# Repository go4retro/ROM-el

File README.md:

# ROM Eliminator (ROM-el)

FLASH ROM replacement devices for various ROM and EPROM familes.

## 2364 ROM-el

## 23128 ROM-el

## 3264 and 23128 ROM-el Programming Adapter

## TCS531000 ROM-el

## HN61256 ROM-el

## HN61256 Programming Adapter

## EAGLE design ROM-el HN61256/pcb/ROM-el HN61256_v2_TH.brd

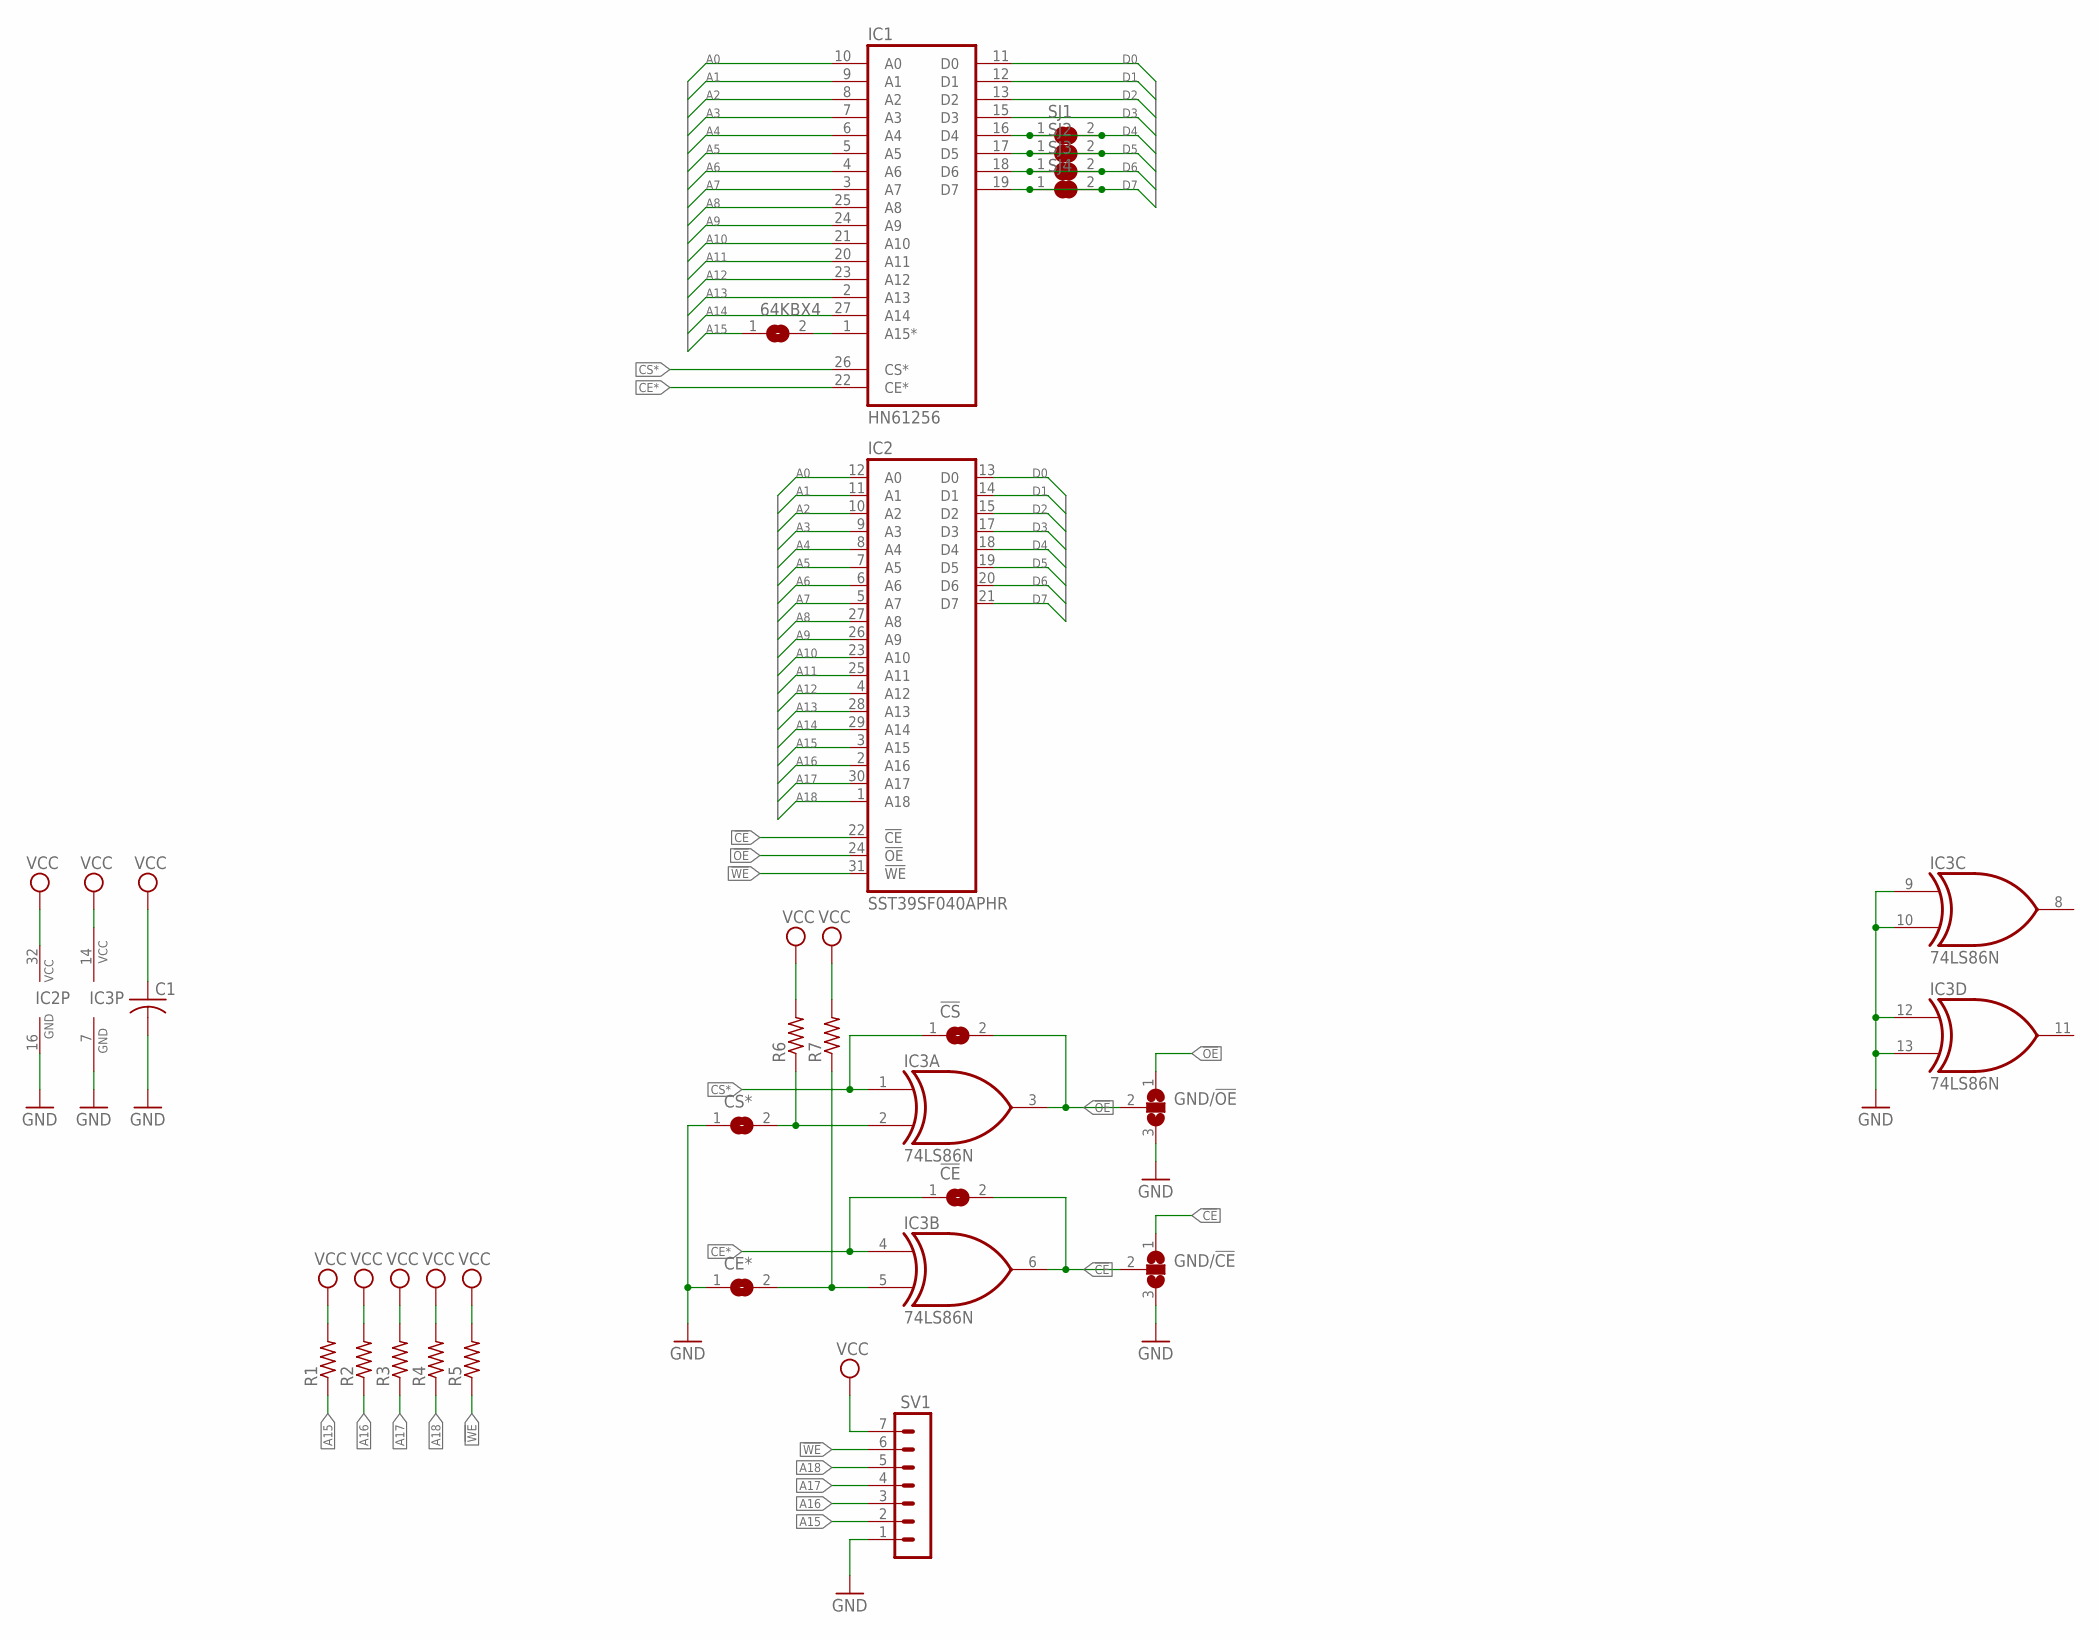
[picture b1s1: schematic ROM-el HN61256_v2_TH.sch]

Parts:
64KBX4: SJ
!CE: SJ
!CS: SJ
C1: C-US025-025X050; C025-025X050
CE*: SJ
CS*: SJ
GND/!CE: SJ2W; SJ_2
GND/!OE: SJ2W; SJ_2
IC1: HN61256; DIL28-6
IC2: SST39SF040APHR; DIL32-RP
IC3: 74LS86N; DIL14-RP
R1, R2, R3, R4, R5, R6, R7: R-US_0204/5; 0204/5
SJ1, SJ2, SJ3, SJ4: SJ
SV1: MA07-1

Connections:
!CE: !CE.2, GND/!CE.1, GND/!CE.2, IC2.22 (!CE), IC3.6 (O)
!OE: !CS.2, GND/!OE.1, GND/!OE.2, IC2.24 (!OE), IC3.3 (O)
!WE: IC2.31 (!WE), R5.1, SV1.6
A0: IC1.10 (A0), IC2.12 (A0)
A1: IC1.9 (A1), IC2.11 (A1)
A2: IC1.8 (A2), IC2.10 (A2)
A3: IC1.7 (A3), IC2.9 (A3)
A4: IC1.6 (A4), IC2.8 (A4)
A5: IC1.5 (A5), IC2.7 (A5)
A6: IC1.4 (A6), IC2.6 (A6)
A7: IC1.3 (A7), IC2.5 (A7)
A8: IC1.25 (A8), IC2.27 (A8)
A9: IC1.24 (A9), IC2.26 (A9)
A10: IC1.21 (A10), IC2.23 (A10)
A11: IC1.20 (A11), IC2.25 (A11)
A12: IC1.23 (A12), IC2.4 (A12)
A13: IC1.2 (A13), IC2.28 (A13)
A14: IC1.27 (A14), IC2.29 (A14)
A15: 64KBX4.1, IC2.3 (A15), R1.1, SV1.2
A16: IC2.2 (A16), R2.1, SV1.3
A17: IC2.30 (A17), R3.1, SV1.4
A18: IC2.1 (A18), R4.1, SV1.5
CE*: !CE.1, IC1.22 (CE*), IC3.4 (I0)
CS*: !CS.1, IC1.26 (CS*), IC3.1 (I0)
D0: IC1.11 (D0), IC2.13 (D0)
D1: IC1.12 (D1), IC2.14 (D1)
D2: IC1.13 (D2), IC2.15 (D2)
D3: IC1.15 (D3), IC2.17 (D3)
D4: IC1.16 (D4), IC2.18 (D4), SJ1.1, SJ1.2
D5: IC1.17 (D5), IC2.19 (D5), SJ2.1, SJ2.2
D6: IC1.18 (D6), IC2.20 (D6), SJ3.1, SJ3.2
D7: IC1.19 (D7), IC2.21 (D7), SJ4.1, SJ4.2
GND: C1.2, CE*.1, CS*.1, GND/!CE.3, GND/!OE.3, IC1.14 (GND), IC2.16 (GND), IC3.7 (GND), IC3.9 (I0), IC3.10 (I1), IC3.12 (I0), IC3.13 (I1), SV1.1
unnamed: 64KBX4.2, IC1.1 (A15*)
unnamed: CS*.2, IC3.2 (I1), R6.1
unnamed: CE*.2, IC3.5 (I1), R7.1
VCC: C1.1, IC1.28 (VCC), IC2.32 (VCC), IC3.14 (VCC), R1.2, R2.2, R3.2, R4.2, R5.2, R6.2, R7.2, SV1.7

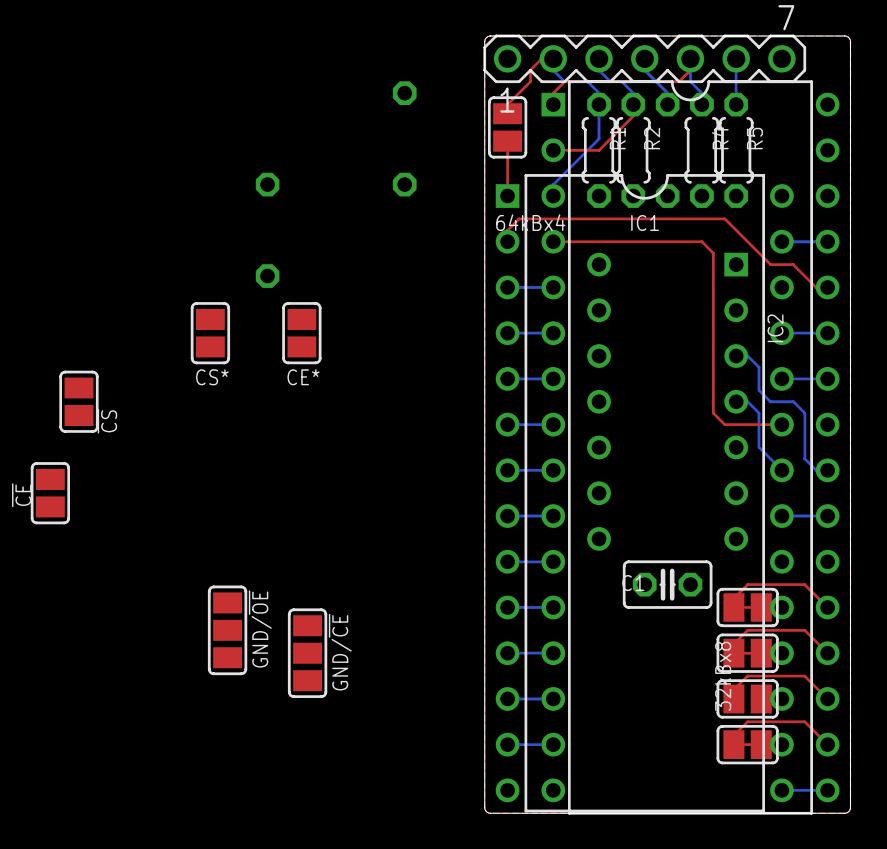
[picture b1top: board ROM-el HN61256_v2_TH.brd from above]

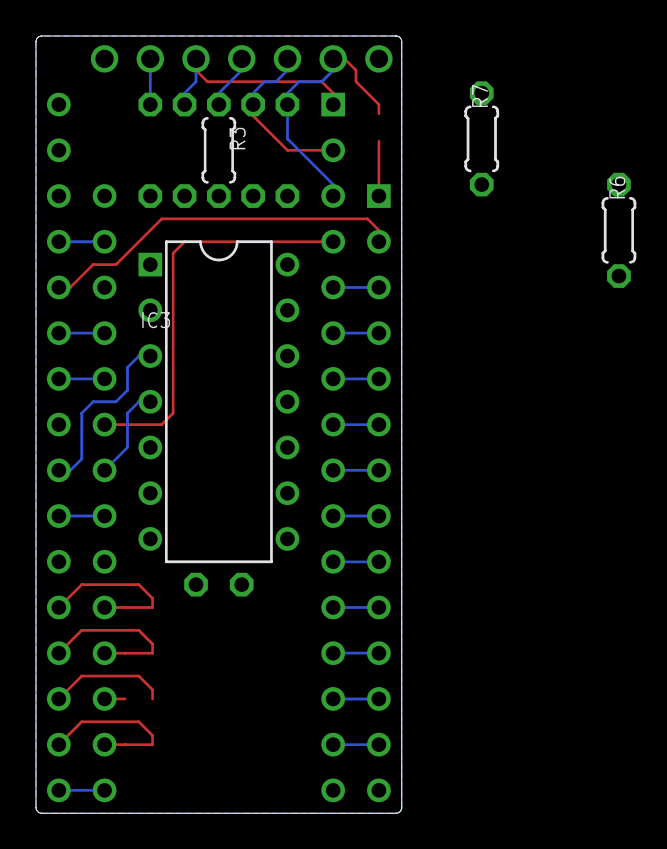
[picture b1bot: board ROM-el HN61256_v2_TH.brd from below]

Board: 2 copper layers, 20.3 x 43.2 mm, 23 parts (4 on the bottom side), 37 nets.

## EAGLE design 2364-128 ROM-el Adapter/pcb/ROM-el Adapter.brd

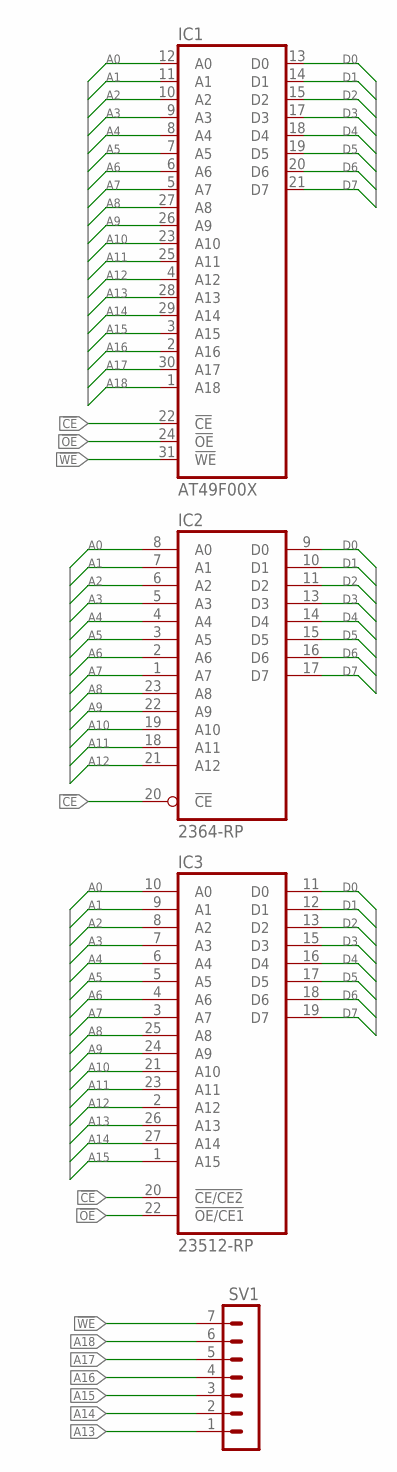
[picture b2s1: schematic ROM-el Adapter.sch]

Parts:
IC1: AT49F00X; DIL32-RP
IC2: 2364-RP; DIL24-ROUNDPAD
IC3: 23512-RP; DIL28-ROUNDPAD
SV1: MA07-1

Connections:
!CE: IC1.22 (!CE), IC2.20 (!CE), IC3.20 (!CE/CE2)
!OE: IC1.24 (!OE), IC3.22 (!OE/CE1)
!WE: IC1.31 (!WE), SV1.7
A0: IC1.12 (A0), IC2.8 (A0), IC3.10 (A0)
A1: IC1.11 (A1), IC2.7 (A1), IC3.9 (A1)
A2: IC1.10 (A2), IC2.6 (A2), IC3.8 (A2)
A3: IC1.9 (A3), IC2.5 (A3), IC3.7 (A3)
A4: IC1.8 (A4), IC2.4 (A4), IC3.6 (A4)
A5: IC1.7 (A5), IC2.3 (A5), IC3.5 (A5)
A6: IC1.6 (A6), IC2.2 (A6), IC3.4 (A6)
A7: IC1.5 (A7), IC2.1 (A7), IC3.3 (A7)
A8: IC1.27 (A8), IC2.23 (A8), IC3.25 (A8)
A9: IC1.26 (A9), IC2.22 (A9), IC3.24 (A9)
A10: IC1.23 (A10), IC2.19 (A10), IC3.21 (A10)
A11: IC1.25 (A11), IC2.18 (A11), IC3.23 (A11)
A12: IC1.4 (A12), IC2.21 (A12), IC3.2 (A12)
A13: IC1.28 (A13), IC3.26 (A13), SV1.1
A14: IC1.29 (A14), IC3.27 (A14), SV1.2
A15: IC1.3 (A15), IC3.1 (A15), SV1.3
A16: IC1.2 (A16), SV1.4
A17: IC1.30 (A17), SV1.5
A18: IC1.1 (A18), SV1.6
D0: IC1.13 (D0), IC2.9 (D0), IC3.11 (D0)
D1: IC1.14 (D1), IC2.10 (D1), IC3.12 (D1)
D2: IC1.15 (D2), IC2.11 (D2), IC3.13 (D2)
D3: IC1.17 (D3), IC2.13 (D3), IC3.15 (D3)
D4: IC1.18 (D4), IC2.14 (D4), IC3.16 (D4)
D5: IC1.19 (D5), IC2.15 (D5), IC3.17 (D5)
D6: IC1.20 (D6), IC2.16 (D6), IC3.18 (D6)
D7: IC1.21 (D7), IC2.17 (D7), IC3.19 (D7)
GND: IC1.16 (GND), IC2.12 (GND), IC3.14 (GND)
VCC: IC1.32 (VCC), IC2.24 (VCC), IC3.28 (VCC)

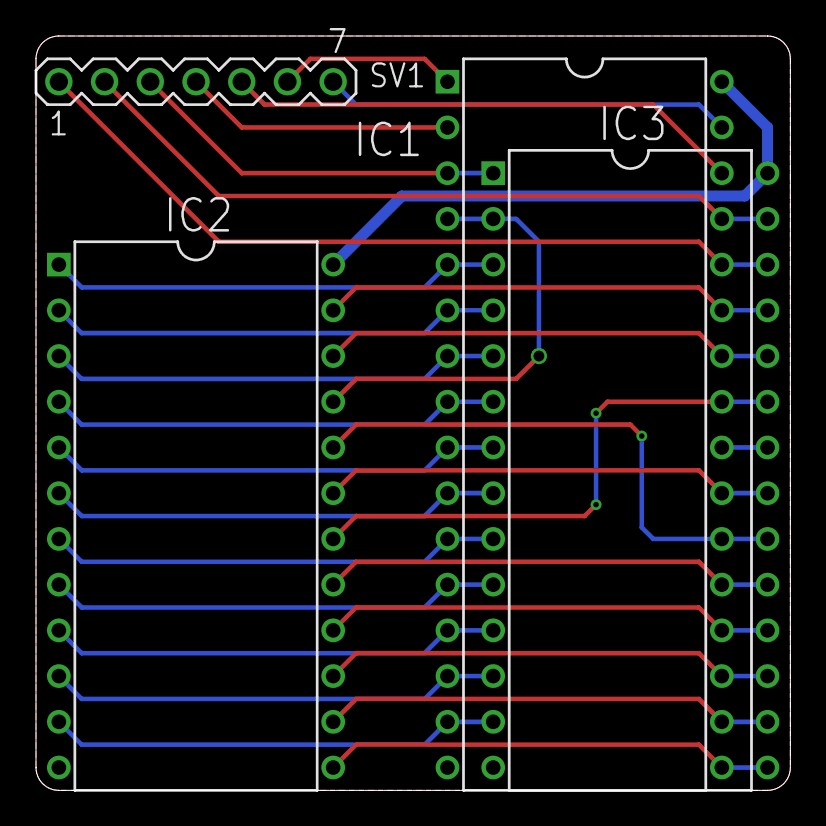
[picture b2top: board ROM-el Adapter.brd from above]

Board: 2 copper layers, 41.9 x 41.9 mm, 4 parts (0 on the bottom side), 32 nets.

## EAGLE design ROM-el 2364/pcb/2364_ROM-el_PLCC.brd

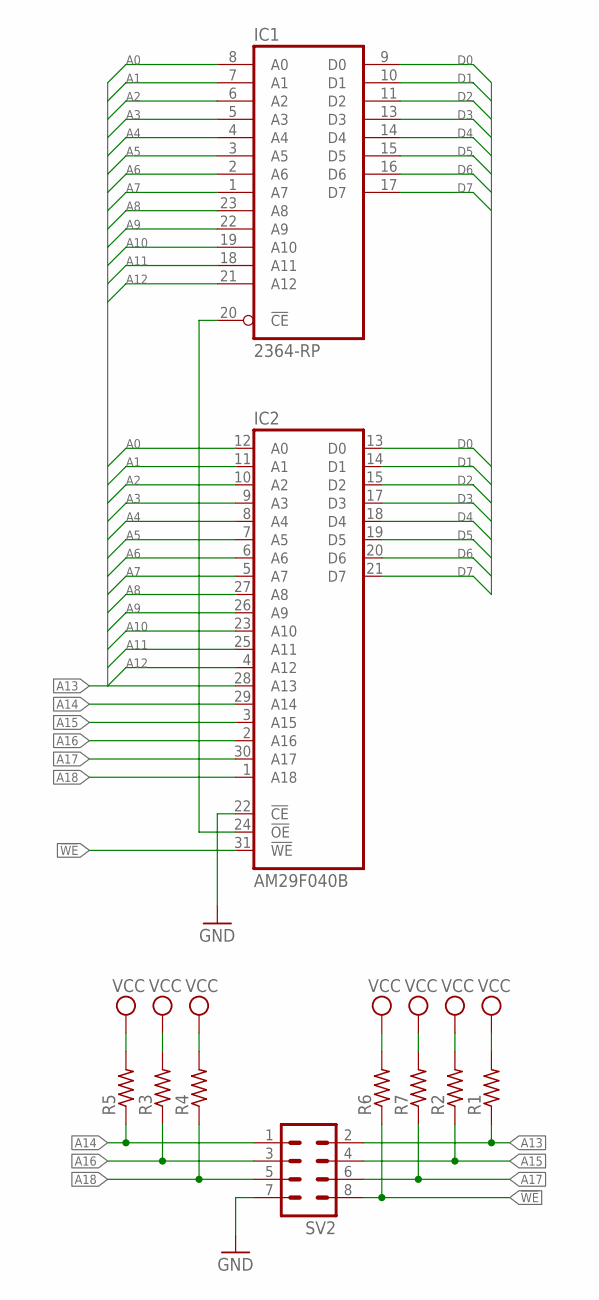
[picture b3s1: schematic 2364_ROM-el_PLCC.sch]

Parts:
IC1: 2364-RP; DIL24-ROUNDPAD
IC2: AM29F040B; PLCC32R
R1, R2, R3, R4, R5, R6, R7: R-US_R0402; R0402
SV2: MA04-2

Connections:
!OE: IC1.20 (!CE), IC2.24 (!OE)
!WE: IC2.31 (!WE), R6.1, SV2.8
A0: IC1.8 (A0), IC2.12 (A0)
A1: IC1.7 (A1), IC2.11 (A1)
A2: IC1.6 (A2), IC2.10 (A2)
A3: IC1.5 (A3), IC2.9 (A3)
A4: IC1.4 (A4), IC2.8 (A4)
A5: IC1.3 (A5), IC2.7 (A5)
A6: IC1.2 (A6), IC2.6 (A6)
A7: IC1.1 (A7), IC2.5 (A7)
A8: IC1.23 (A8), IC2.27 (A8)
A9: IC1.22 (A9), IC2.26 (A9)
A10: IC1.19 (A10), IC2.23 (A10)
A11: IC1.18 (A11), IC2.25 (A11)
A12: IC1.21 (A12), IC2.4 (A12)
A13: IC2.28 (A13), R1.1, SV2.2
A14: IC2.29 (A14), R5.1, SV2.1
A15: IC2.3 (A15), R2.1, SV2.4
A16: IC2.2 (A16), R3.1, SV2.3
A17: IC2.30 (A17), R7.1, SV2.6
A18: IC2.1 (A18), R4.1, SV2.5
D0: IC1.9 (D0), IC2.13 (D0)
D1: IC1.10 (D1), IC2.14 (D1)
D2: IC1.11 (D2), IC2.15 (D2)
D3: IC1.13 (D3), IC2.17 (D3)
D4: IC1.14 (D4), IC2.18 (D4)
D5: IC1.15 (D5), IC2.19 (D5)
D6: IC1.16 (D6), IC2.20 (D6)
D7: IC1.17 (D7), IC2.21 (D7)
GND: IC1.12 (GND), IC2.16 (GND), IC2.22 (!CE), SV2.7
VCC: IC1.24 (VCC), IC2.32 (VCC), R1.2, R2.2, R3.2, R4.2, R5.2, R6.2, R7.2

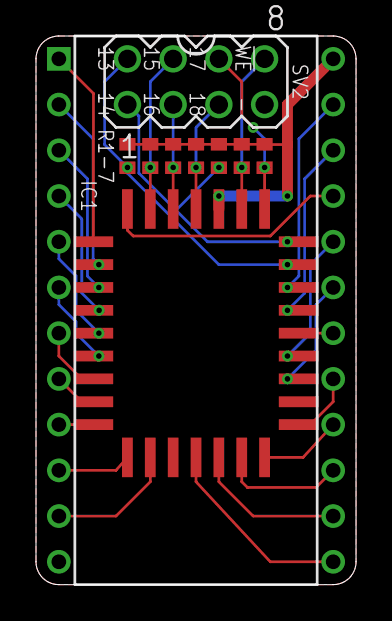
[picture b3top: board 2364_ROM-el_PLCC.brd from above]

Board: 2 copper layers, 17.8 x 30.5 mm, 10 parts (0 on the bottom side), 31 nets.

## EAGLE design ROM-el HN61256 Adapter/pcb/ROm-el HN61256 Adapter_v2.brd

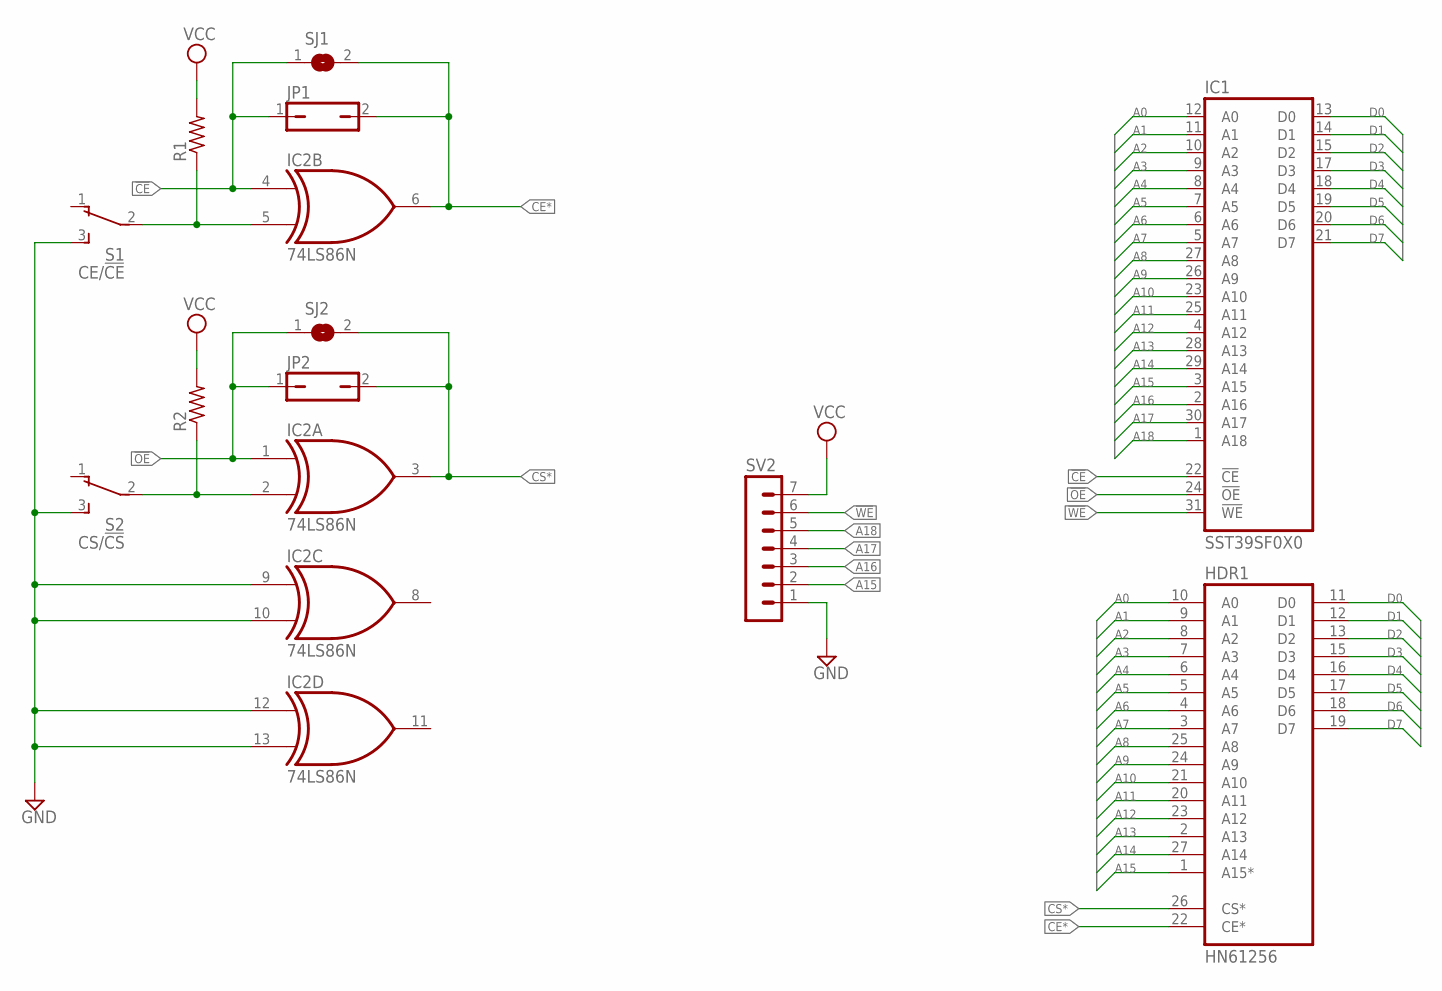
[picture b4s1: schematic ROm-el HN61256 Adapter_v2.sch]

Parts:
HDR1: HN61256; DIL28-6
IC1: SST39SF0X0; DIL32-RP
IC2: 74LS86N; DIL14-RP
JP1, JP2: JP1Q; JP1
R1, R2: R-US_0204/5; 0204/5
S1: CE/!CE; TL3XWO
S2: CS/!CS; TL3XWO
SJ1, SJ2: SJ
SV2: MA07-1

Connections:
!CE: IC1.22 (!CE), IC2.4 (I0), JP1.1, SJ1.1
!OE: IC1.24 (!OE), IC2.1 (I0), JP2.1, SJ2.1
!WE: IC1.31 (!WE), SV2.6
A0: HDR1.10 (A0), IC1.12 (A0)
A1: HDR1.9 (A1), IC1.11 (A1)
A2: HDR1.8 (A2), IC1.10 (A2)
A3: HDR1.7 (A3), IC1.9 (A3)
A4: HDR1.6 (A4), IC1.8 (A4)
A5: HDR1.5 (A5), IC1.7 (A5)
A6: HDR1.4 (A6), IC1.6 (A6)
A7: HDR1.3 (A7), IC1.5 (A7)
A8: HDR1.25 (A8), IC1.27 (A8)
A9: HDR1.24 (A9), IC1.26 (A9)
A10: HDR1.21 (A10), IC1.23 (A10)
A11: HDR1.20 (A11), IC1.25 (A11)
A12: HDR1.23 (A12), IC1.4 (A12)
A13: HDR1.2 (A13), IC1.28 (A13)
A14: HDR1.27 (A14), IC1.29 (A14)
A15: HDR1.1 (A15*), IC1.3 (A15), SV2.2
A16: IC1.2 (A16), SV2.3
A17: IC1.30 (A17), SV2.4
A18: IC1.1 (A18), SV2.5
CE*: HDR1.22 (CE*), IC2.6 (O), JP1.2, SJ1.2
CS*: HDR1.26 (CS*), IC2.3 (O), JP2.2, SJ2.2
D0: HDR1.11 (D0), IC1.13 (D0)
D1: HDR1.12 (D1), IC1.14 (D1)
D2: HDR1.13 (D2), IC1.15 (D2)
D3: HDR1.15 (D3), IC1.17 (D3)
D4: HDR1.16 (D4), IC1.18 (D4)
D5: HDR1.17 (D5), IC1.19 (D5)
D6: HDR1.18 (D6), IC1.20 (D6)
D7: HDR1.19 (D7), IC1.21 (D7)
GND: HDR1.14 (GND), IC1.16 (GND), IC2.7 (GND), IC2.9 (I0), IC2.10 (I1), IC2.12 (I0), IC2.13 (I1), S1.3 (S), S2.3 (S), SV2.1
unnamed: IC2.2 (I1), R2.1, S2.2
unnamed: IC2.5 (I1), R1.1, S1.2
VCC: HDR1.28 (VCC), IC1.32 (VCC), IC2.14 (VCC), R1.2, R2.2, SV2.7

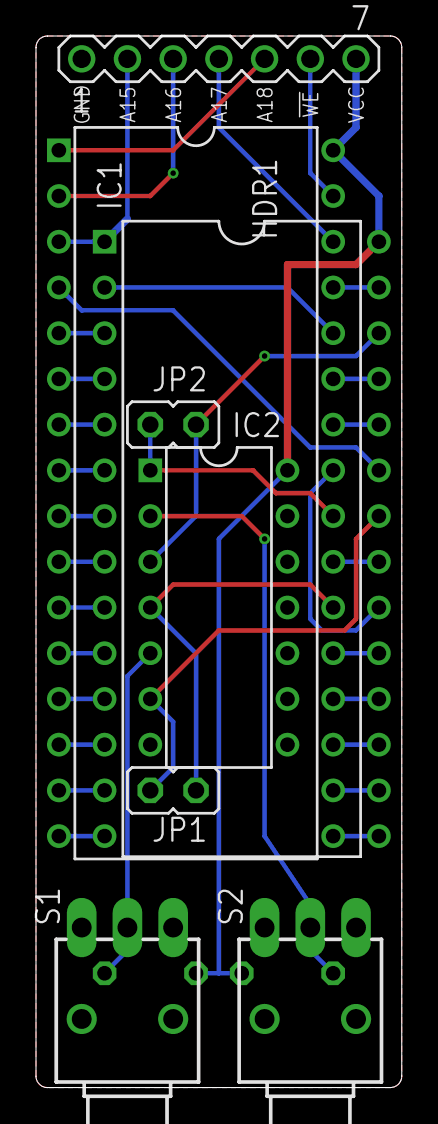
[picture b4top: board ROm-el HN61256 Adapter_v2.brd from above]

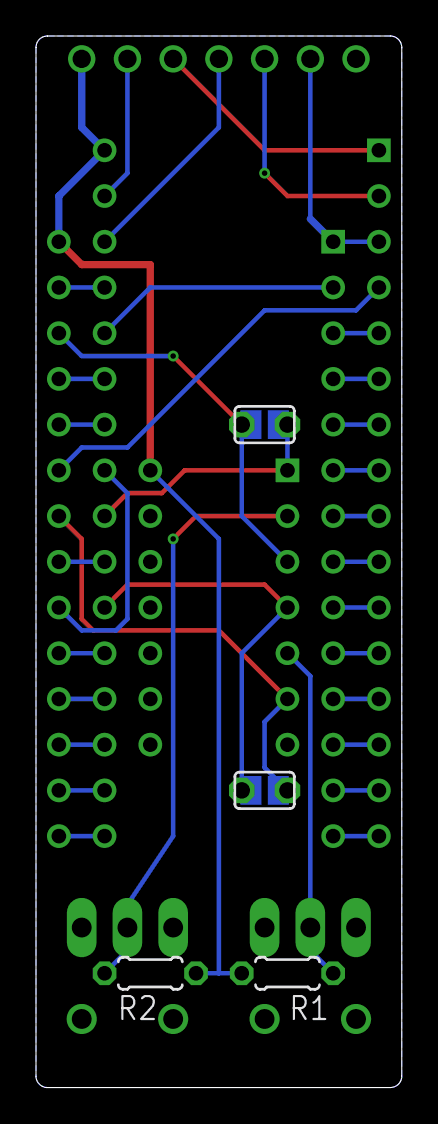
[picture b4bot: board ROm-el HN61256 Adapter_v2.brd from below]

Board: 2 copper layers, 20.3 x 58.4 mm, 12 parts (4 on the bottom side), 36 nets.

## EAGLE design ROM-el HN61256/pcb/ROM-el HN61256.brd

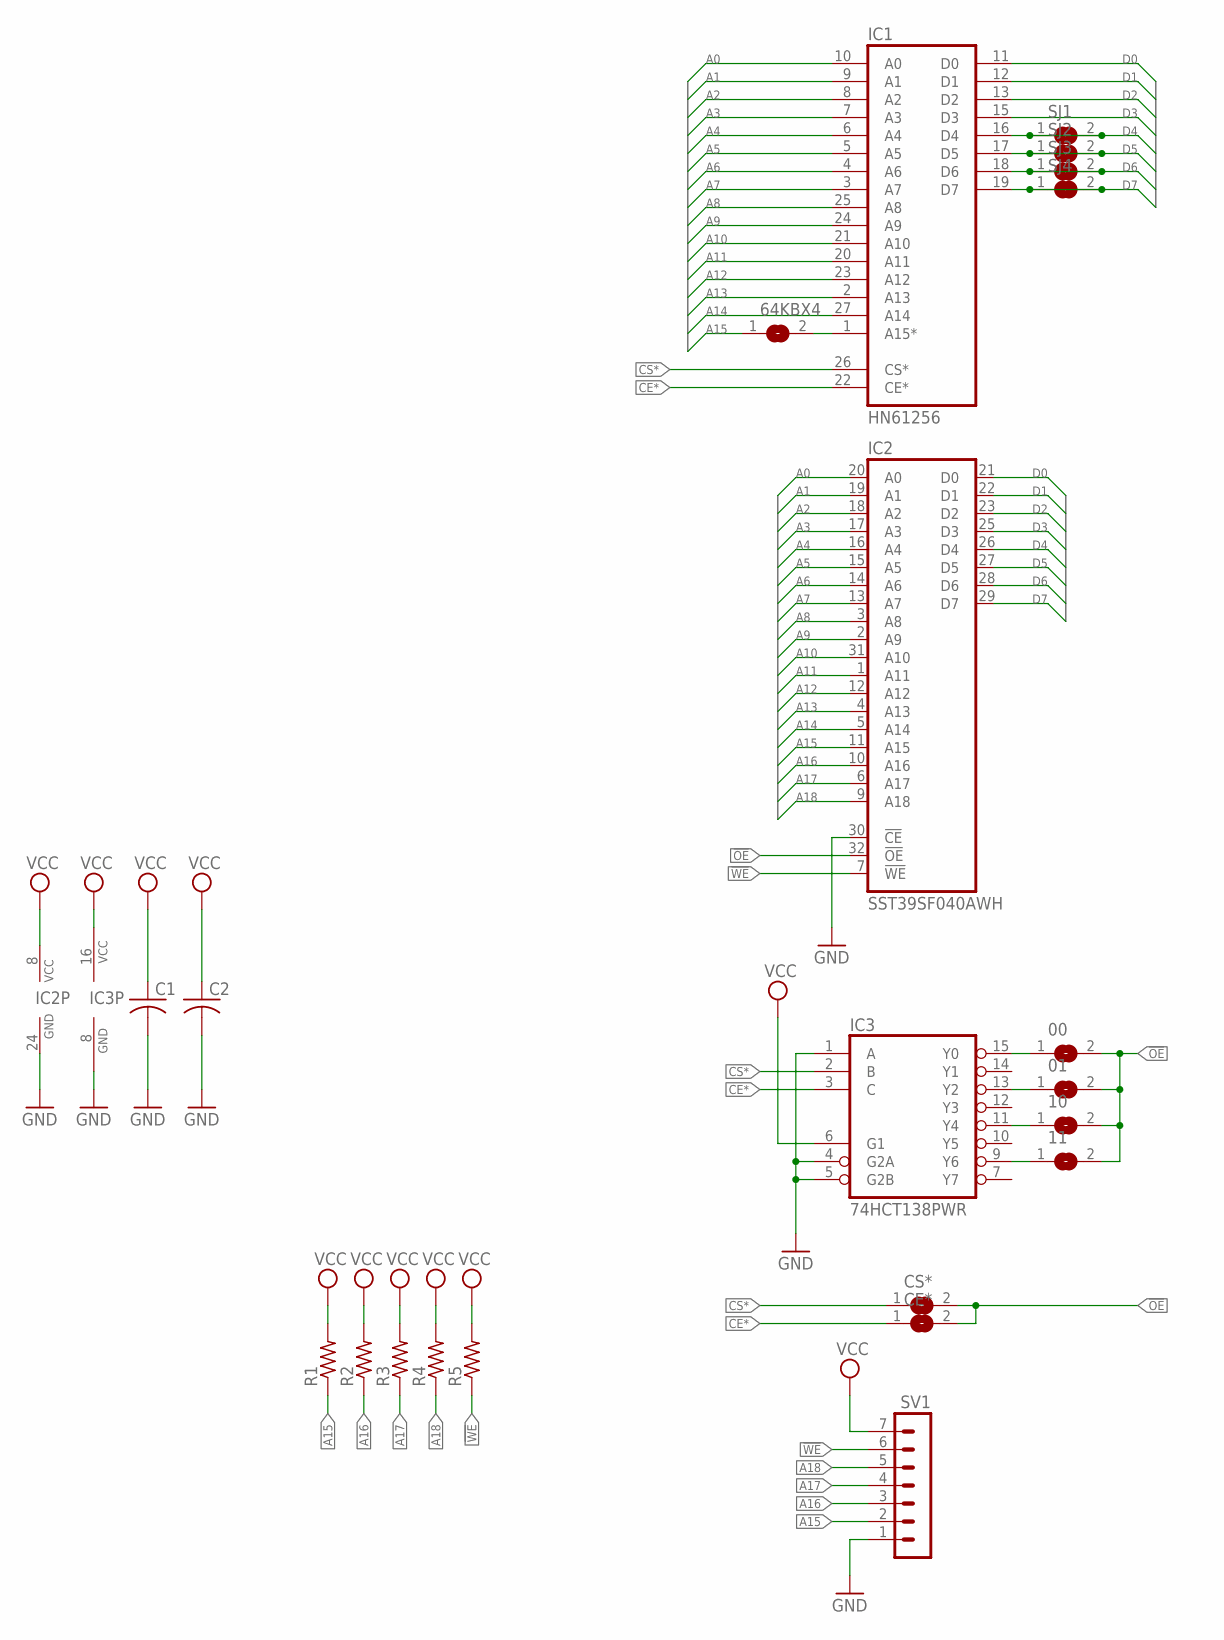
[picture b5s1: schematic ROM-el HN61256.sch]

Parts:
00, 01, 10, 11, 64KBX4: SJ
C1, C2: C-USC0402; C0402
CE*: SJ
CS*: SJ
IC1: HN61256; DIL28-6
IC2: SST39SF040AWH; VSOP32
IC3: 74HCT138PWR; TSSOP16
R1, R2, R3, R4, R5: R-US_R0402; R0402
SJ1, SJ2, SJ3, SJ4: SJ
SV1: MA07-1

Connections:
!OE: 00.2, 01.2, 10.2, 11.2, CE*.2, CS*.2, IC2.32 (!OE)
!WE: IC2.7 (!WE), R5.1, SV1.6
A0: IC1.10 (A0), IC2.20 (A0)
A1: IC1.9 (A1), IC2.19 (A1)
A2: IC1.8 (A2), IC2.18 (A2)
A3: IC1.7 (A3), IC2.17 (A3)
A4: IC1.6 (A4), IC2.16 (A4)
A5: IC1.5 (A5), IC2.15 (A5)
A6: IC1.4 (A6), IC2.14 (A6)
A7: IC1.3 (A7), IC2.13 (A7)
A8: IC1.25 (A8), IC2.3 (A8)
A9: IC1.24 (A9), IC2.2 (A9)
A10: IC1.21 (A10), IC2.31 (A10)
A11: IC1.20 (A11), IC2.1 (A11)
A12: IC1.23 (A12), IC2.12 (A12)
A13: IC1.2 (A13), IC2.4 (A13)
A14: IC1.27 (A14), IC2.5 (A14)
A15: 64KBX4.1, IC2.11 (A15), R1.1, SV1.2
A16: IC2.10 (A16), R2.1, SV1.3
A17: IC2.6 (A17), R3.1, SV1.4
A18: IC2.9 (A18), R4.1, SV1.5
CE*: CE*.1, IC1.22 (CE*), IC3.3 (C)
CS*: CS*.1, IC1.26 (CS*), IC3.2 (B)
D0: IC1.11 (D0), IC2.21 (D0)
D1: IC1.12 (D1), IC2.22 (D1)
D2: IC1.13 (D2), IC2.23 (D2)
D3: IC1.15 (D3), IC2.25 (D3)
D4: IC1.16 (D4), IC2.26 (D4), SJ1.1, SJ1.2
D5: IC1.17 (D5), IC2.27 (D5), SJ2.1, SJ2.2
D6: IC1.18 (D6), IC2.28 (D6), SJ3.1, SJ3.2
D7: IC1.19 (D7), IC2.29 (D7), SJ4.1, SJ4.2
GND: C1.2, C2.2, IC1.14 (GND), IC2.24 (GND), IC2.30 (!CE), IC3.1 (A), IC3.4 (G2A), IC3.5 (G2B), IC3.8 (GND), SV1.1
unnamed: 64KBX4.2, IC1.1 (A15*)
unnamed: 11.1, IC3.9 (Y6)
unnamed: 10.1, IC3.11 (Y4)
unnamed: 01.1, IC3.13 (Y2)
unnamed: 00.1, IC3.15 (Y0)
VCC: C1.1, C2.1, IC1.28 (VCC), IC2.8 (VCC), IC3.6 (G1), IC3.16 (VCC), R1.2, R2.2, R3.2, R4.2, R5.2, SV1.7

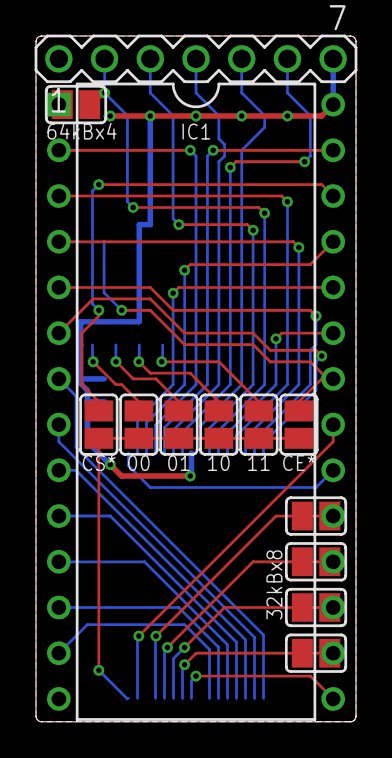
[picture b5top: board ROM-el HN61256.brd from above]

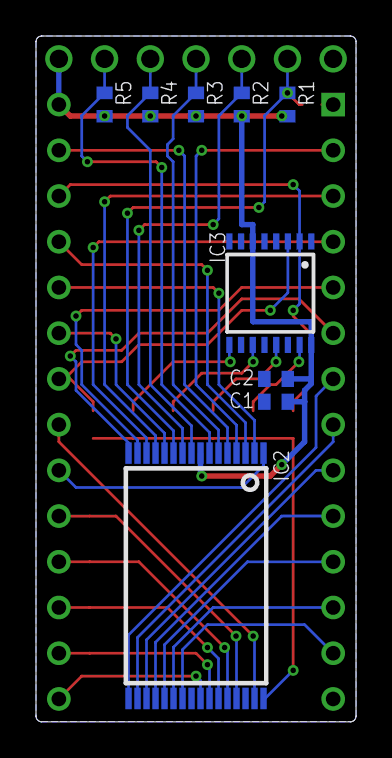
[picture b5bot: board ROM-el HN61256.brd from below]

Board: 2 copper layers, 17.8 x 38.1 mm, 22 parts (9 on the bottom side), 38 nets.

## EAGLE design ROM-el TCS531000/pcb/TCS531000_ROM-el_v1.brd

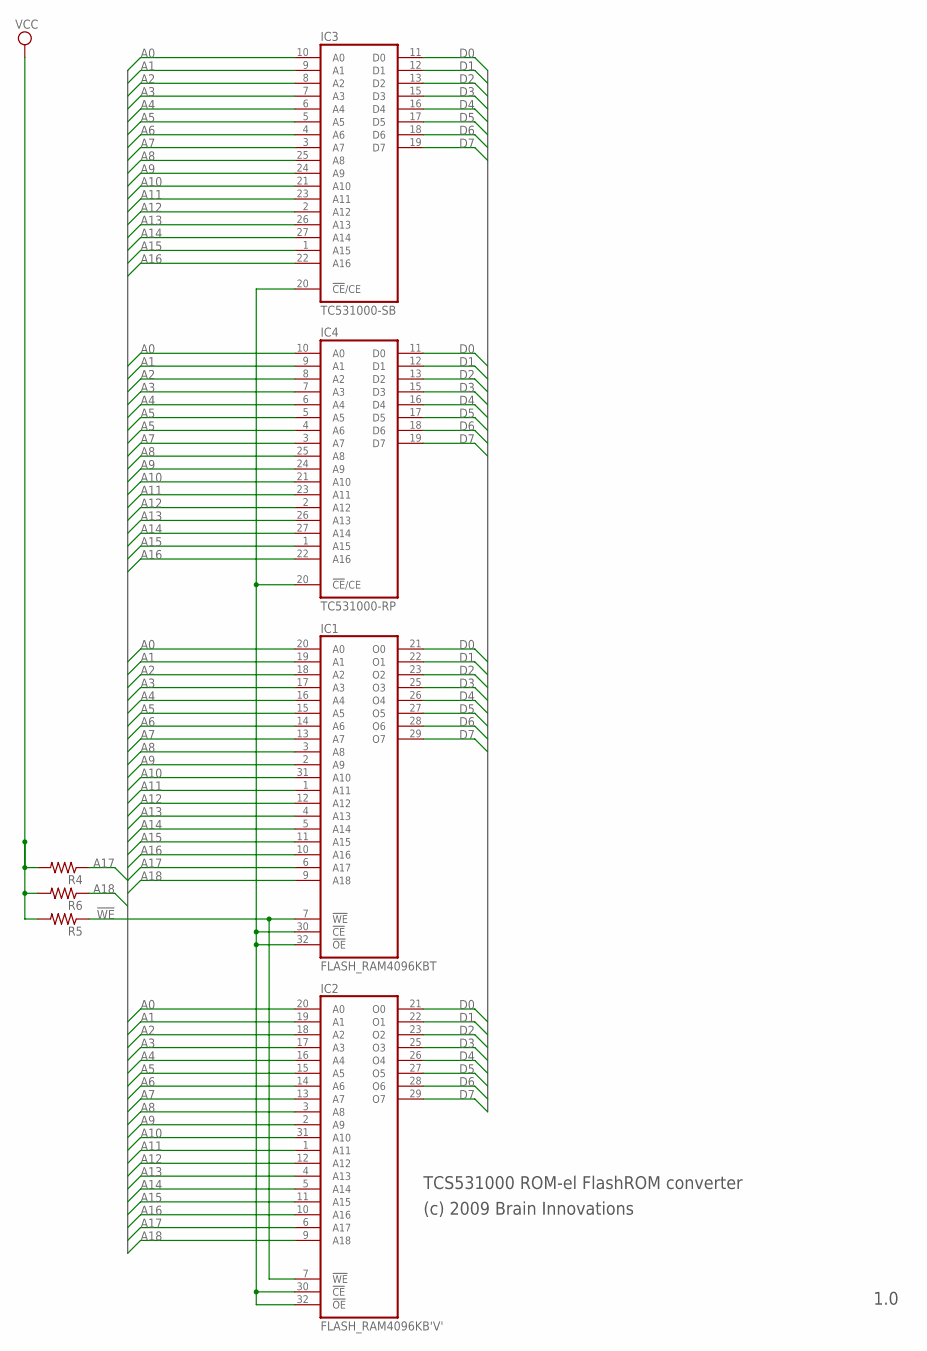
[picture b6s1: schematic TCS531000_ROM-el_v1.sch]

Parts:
IC1: FLASH_RAM4096KBT; TSOP32
IC2: FLASH_RAM4096KB'V'; VSOP32
IC3: TC531000-SB; DIL28-SMD-REVERSE
IC4: TC531000-RP; DIL28-ROUNDPAD
R4, R5, R6: R-US_R0805; R0805

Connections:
!WE: IC1.7 (!WE), IC2.7 (!WE), R5.1
A0: IC1.20 (A0), IC2.20 (A0), IC3.10 (A0), IC4.10 (A0)
A1: IC1.19 (A1), IC2.19 (A1), IC3.9 (A1), IC4.9 (A1)
A2: IC1.18 (A2), IC2.18 (A2), IC3.8 (A2), IC4.8 (A2)
A3: IC1.17 (A3), IC2.17 (A3), IC3.7 (A3), IC4.7 (A3)
A4: IC1.16 (A4), IC2.16 (A4), IC3.6 (A4), IC4.6 (A4)
A5: IC1.15 (A5), IC2.15 (A5), IC3.5 (A5), IC4.5 (A5)
A6: IC1.14 (A6), IC2.14 (A6), IC3.4 (A6), IC4.4 (A6)
A7: IC1.13 (A7), IC2.13 (A7), IC3.3 (A7), IC4.3 (A7)
A8: IC1.3 (A8), IC2.3 (A8), IC3.25 (A8), IC4.25 (A8)
A9: IC1.2 (A9), IC2.2 (A9), IC3.24 (A9), IC4.24 (A9)
A10: IC1.31 (A10), IC2.31 (A10), IC3.21 (A10), IC4.21 (A10)
A11: IC1.1 (A11), IC2.1 (A11), IC3.23 (A11), IC4.23 (A11)
A12: IC1.12 (A12), IC2.12 (A12), IC3.2 (A12), IC4.2 (A12)
A13: IC1.4 (A13), IC2.4 (A13), IC3.26 (A13), IC4.26 (A13)
A14: IC1.5 (A14), IC2.5 (A14), IC3.27 (A14), IC4.27 (A14)
A15: IC1.11 (A15), IC2.11 (A15), IC3.1 (A15), IC4.1 (A15)
A16: IC1.10 (A16), IC2.10 (A16), IC3.22 (A16), IC4.22 (A16)
A17: IC1.6 (A17), IC2.6 (A17), R4.1
A18: IC1.9 (A18), IC2.9 (A18), R6.1
D0: IC1.21 (O0), IC2.21 (O0), IC3.11 (D0), IC4.11 (D0)
D1: IC1.22 (O1), IC2.22 (O1), IC3.12 (D1), IC4.12 (D1)
D2: IC1.23 (O2), IC2.23 (O2), IC3.13 (D2), IC4.13 (D2)
D3: IC1.25 (O3), IC2.25 (O3), IC3.15 (D3), IC4.15 (D3)
D4: IC1.26 (O4), IC2.26 (O4), IC3.16 (D4), IC4.16 (D4)
D5: IC1.27 (O5), IC2.27 (O5), IC3.17 (D5), IC4.17 (D5)
D6: IC1.28 (O6), IC2.28 (O6), IC3.18 (D6), IC4.18 (D6)
D7: IC1.29 (O7), IC2.29 (O7), IC3.19 (D7), IC4.19 (D7)
GND: IC1.24 (GND), IC2.24 (GND), IC3.14 (GND), IC4.14 (GND)
unnamed: IC1.30 (!CE), IC1.32 (!OE), IC2.30 (!CE), IC2.32 (!OE), IC3.20 (!CE!/CE), IC4.20 (!CE!/CE)
VCC: IC1.8 (VCC), IC2.8 (VCC), IC3.28 (VCC), IC4.28 (VCC), R4.2, R5.2, R6.2

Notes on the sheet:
(c) 2009 Brain Innovations
TCS531000 ROM-el FlashROM converter
1.0

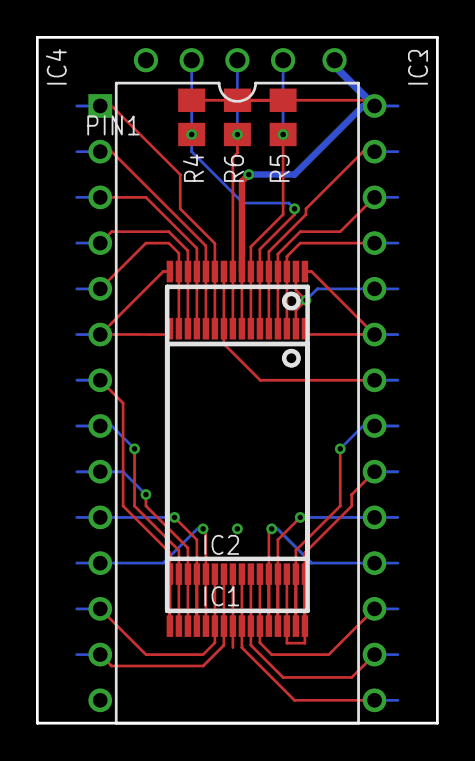
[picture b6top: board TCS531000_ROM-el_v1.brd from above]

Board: 2 copper layers, 22.2 x 38.1 mm, 7 parts (0 on the bottom side), 31 nets.

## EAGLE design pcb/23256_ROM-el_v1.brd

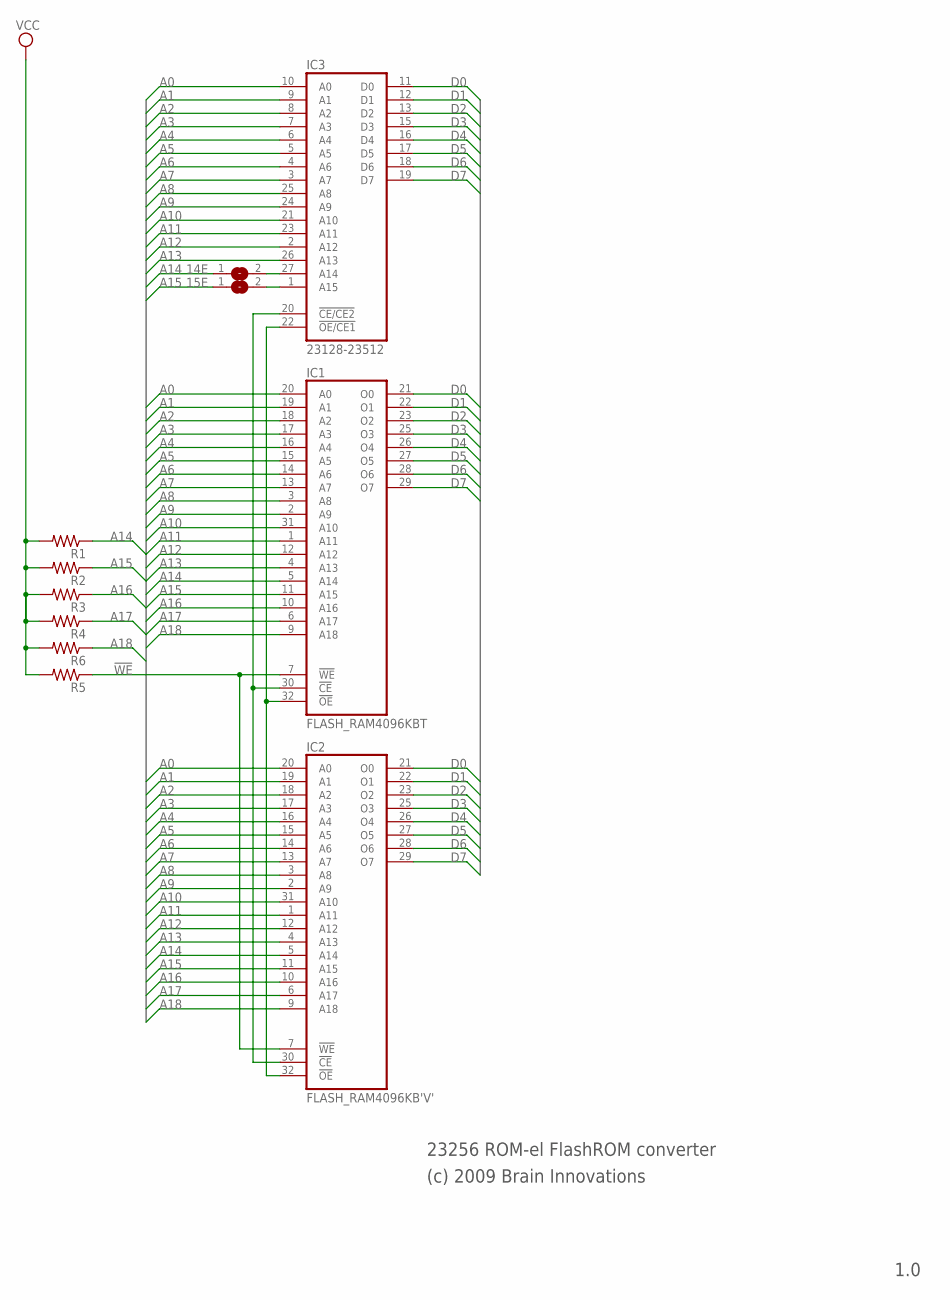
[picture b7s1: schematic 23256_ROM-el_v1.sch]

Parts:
14E: SJ
15E: 15E; SJ
IC1: FLASH_RAM4096KBT; TSOP32
IC2: FLASH_RAM4096KB'V'; VSOP32
IC3: 23128-23512; DIL28-ROUNDPAD
R1, R2, R3, R4, R5, R6: R-US_R0805; R0805

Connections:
!WE: IC1.7 (!WE), IC2.7 (!WE), R5.1
A0: IC1.20 (A0), IC2.20 (A0), IC3.10 (A0)
A1: IC1.19 (A1), IC2.19 (A1), IC3.9 (A1)
A2: IC1.18 (A2), IC2.18 (A2), IC3.8 (A2)
A3: IC1.17 (A3), IC2.17 (A3), IC3.7 (A3)
A4: IC1.16 (A4), IC2.16 (A4), IC3.6 (A4)
A5: IC1.15 (A5), IC2.15 (A5), IC3.5 (A5)
A6: IC1.14 (A6), IC2.14 (A6), IC3.4 (A6)
A7: IC1.13 (A7), IC2.13 (A7), IC3.3 (A7)
A8: IC1.3 (A8), IC2.3 (A8), IC3.25 (A8)
A9: IC1.2 (A9), IC2.2 (A9), IC3.24 (A9)
A10: IC1.31 (A10), IC2.31 (A10), IC3.21 (A10)
A11: IC1.1 (A11), IC2.1 (A11), IC3.23 (A11)
A12: IC1.12 (A12), IC2.12 (A12), IC3.2 (A12)
A13: IC1.4 (A13), IC2.4 (A13), IC3.26 (A13)
A14: 14E.1, IC1.5 (A14), IC2.5 (A14), R1.1
A15: 15E.1, IC1.11 (A15), IC2.11 (A15), R2.1
A16: IC1.10 (A16), IC2.10 (A16), R3.1
A17: IC1.6 (A17), IC2.6 (A17), R4.1
A18: IC1.9 (A18), IC2.9 (A18), R6.1
D0: IC1.21 (O0), IC2.21 (O0), IC3.11 (D0)
D1: IC1.22 (O1), IC2.22 (O1), IC3.12 (D1)
D2: IC1.23 (O2), IC2.23 (O2), IC3.13 (D2)
D3: IC1.25 (O3), IC2.25 (O3), IC3.15 (D3)
D4: IC1.26 (O4), IC2.26 (O4), IC3.16 (D4)
D5: IC1.27 (O5), IC2.27 (O5), IC3.17 (D5)
D6: IC1.28 (O6), IC2.28 (O6), IC3.18 (D6)
D7: IC1.29 (O7), IC2.29 (O7), IC3.19 (D7)
GND: IC1.24 (GND), IC2.24 (GND), IC3.14 (GND)
unnamed: IC1.32 (!OE), IC2.32 (!OE), IC3.22 (!OE/CE1)
unnamed: IC1.30 (!CE), IC2.30 (!CE), IC3.20 (!CE/CE2)
unnamed: 14E.2, IC3.27 (A14)
unnamed: 15E.2, IC3.1 (A15)
VCC: IC1.8 (VCC), IC2.8 (VCC), IC3.28 (VCC), R1.2, R2.2, R3.2, R4.2, R5.2, R6.2

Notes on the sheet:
(c) 2009 Brain Innovations
23256 ROM-el FlashROM converter
1.0

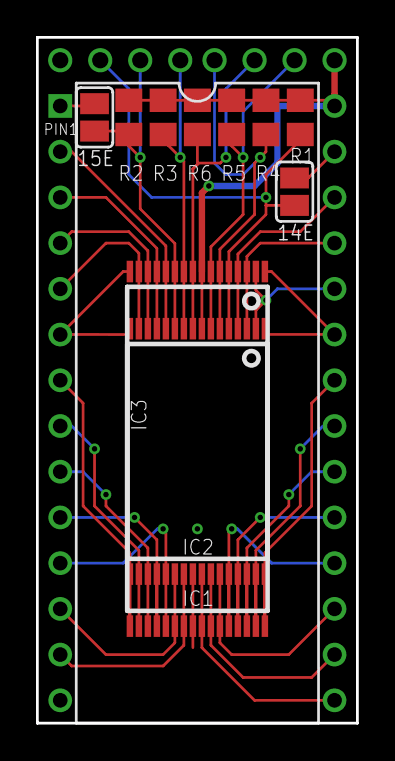
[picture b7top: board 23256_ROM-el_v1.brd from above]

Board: 2 copper layers, 17.8 x 38.1 mm, 11 parts (0 on the bottom side), 34 nets.

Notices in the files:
ROM-el TCS531000/pcb/TCS531000_ROM-el_v1.brd:
(c)2025 RETRO Innovations
pcb/23256_ROM-el_v1.brd:
(c)2009-11 RETRO Innovations
pcb/2364_ROM-el_v1.1.brd:
(c)2009-17 RETRO Innovations
